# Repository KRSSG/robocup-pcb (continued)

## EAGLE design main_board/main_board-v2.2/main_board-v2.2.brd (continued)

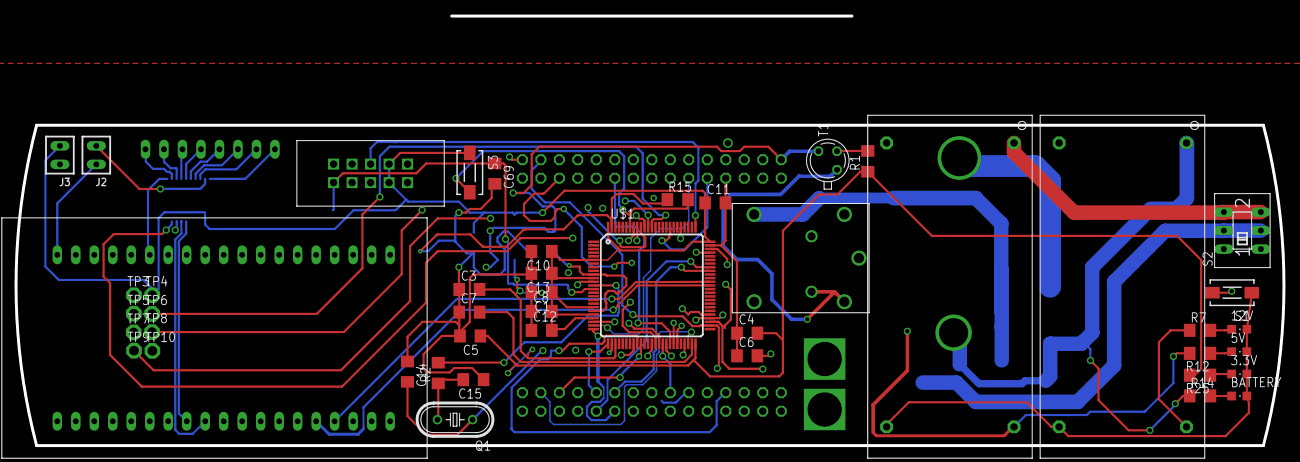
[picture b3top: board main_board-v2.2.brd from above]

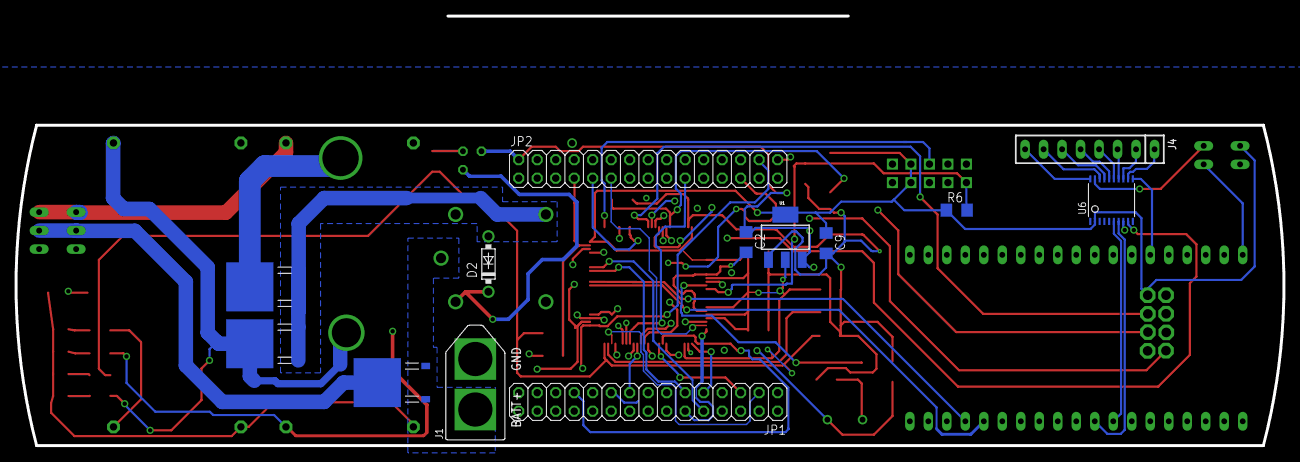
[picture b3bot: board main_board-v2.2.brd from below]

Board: 4 copper layers, 174.2 x 44.0 mm, 59 parts (13 on the bottom side), 70 nets.

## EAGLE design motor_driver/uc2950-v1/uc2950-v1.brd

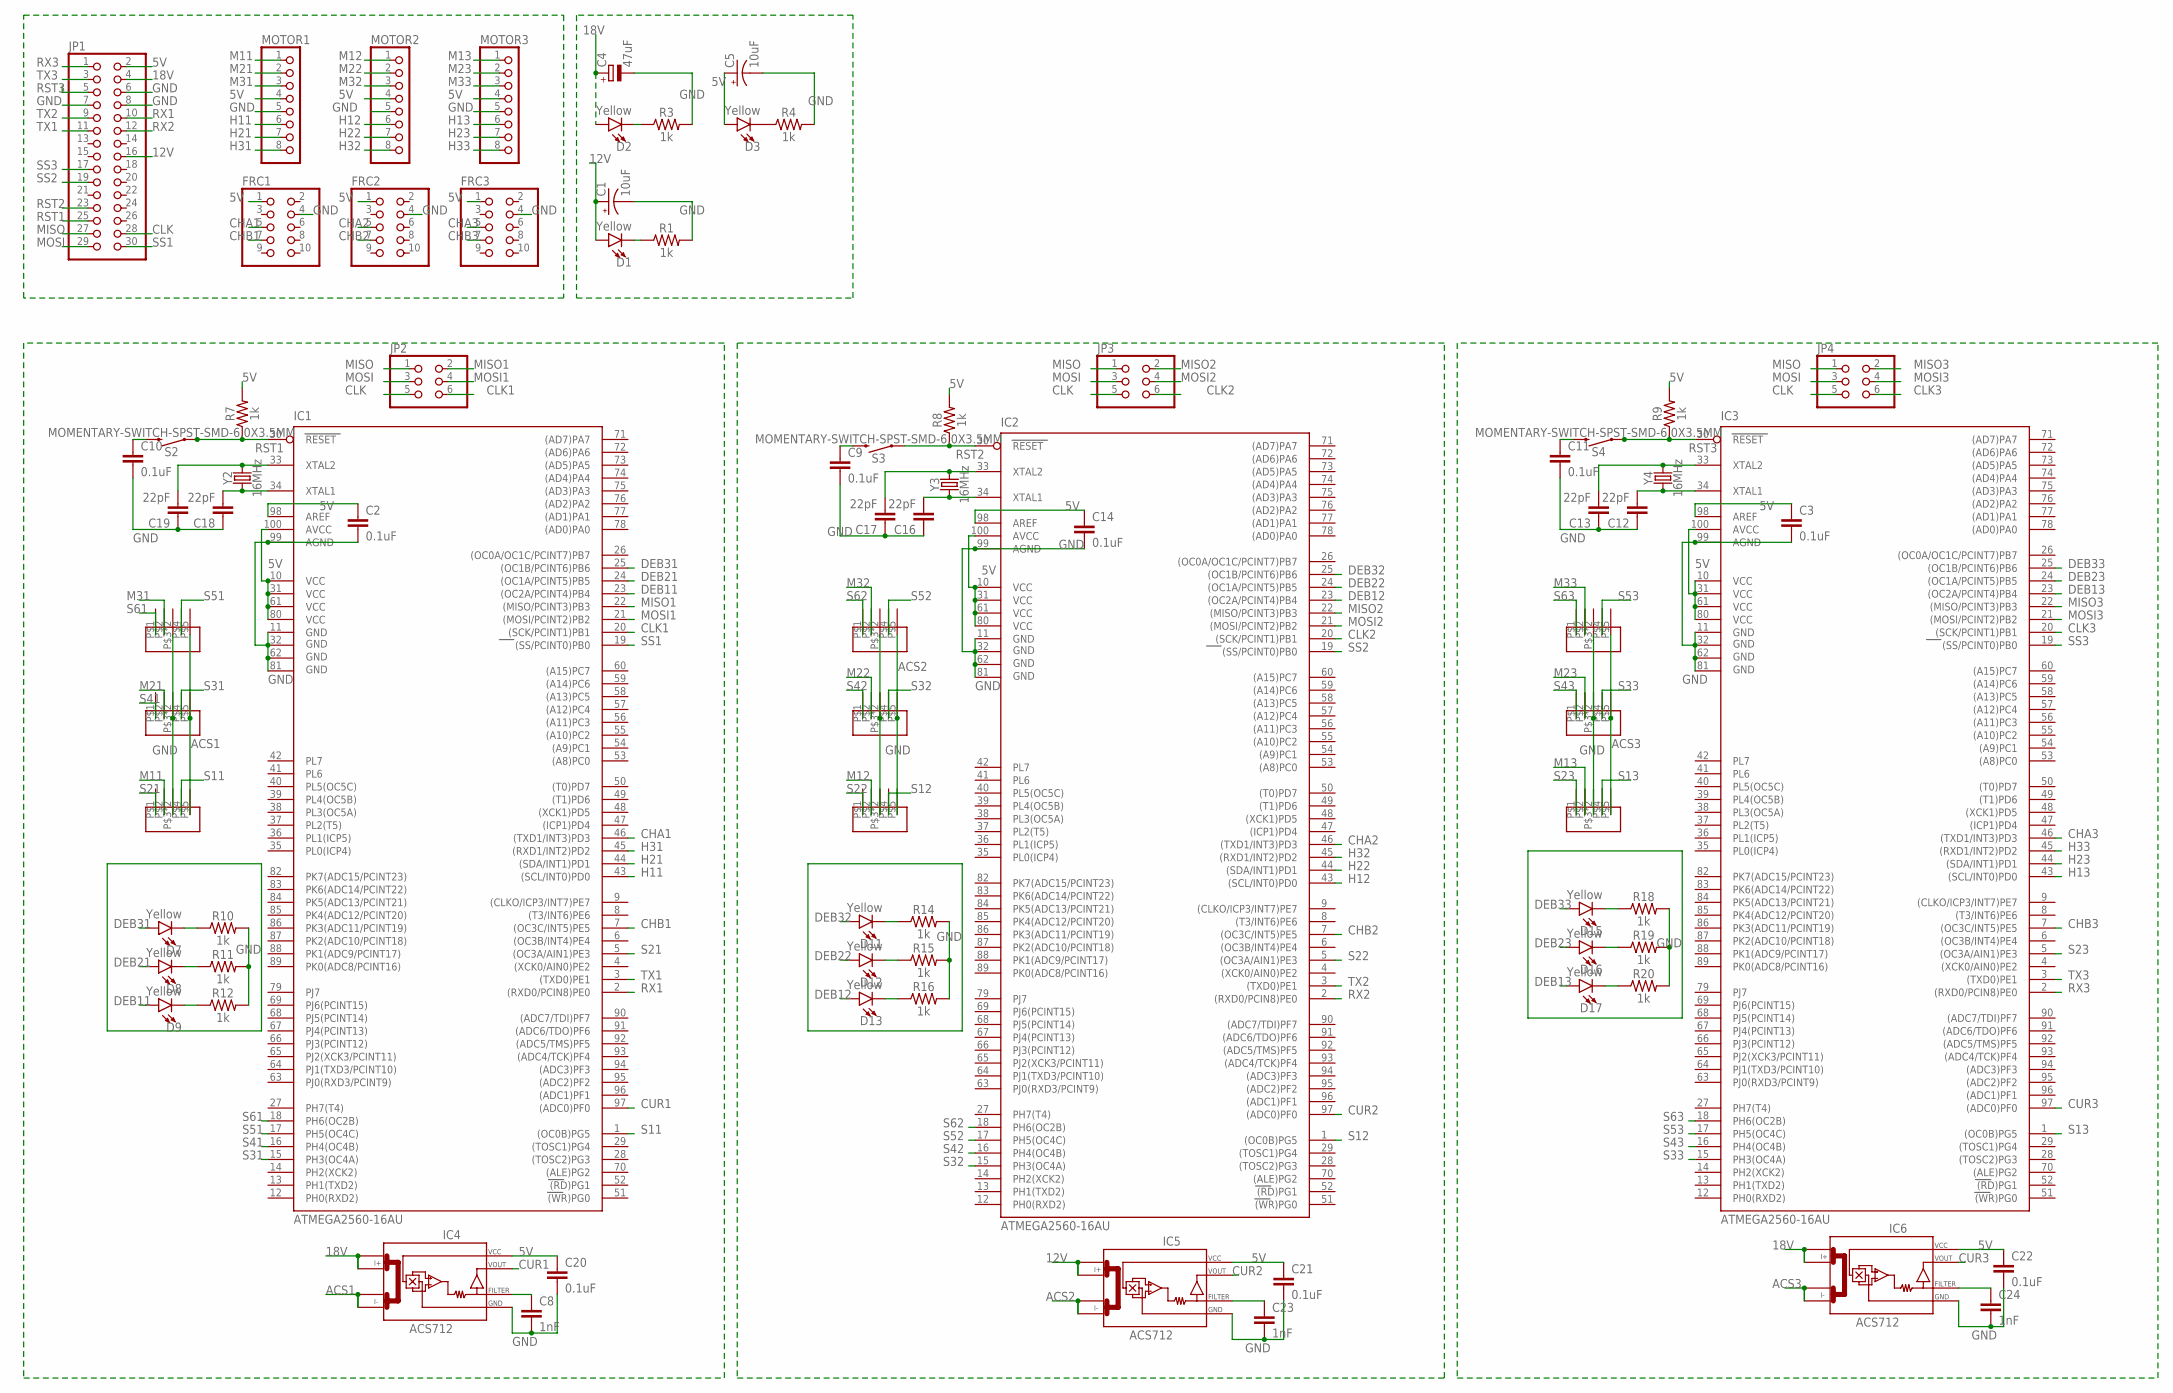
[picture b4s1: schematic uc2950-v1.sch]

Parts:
C1, C5: 10uF; 0603-POLAR
C2, C3, C9, C10, C11, C14, C20, C21, C22: 0.1uF; 0603
C4: 47uF; TAP5-60
C8, C23, C24: 1nF; 0603
C12, C13, C16, C17, C18, C19: 22pF; 0603
D1, D2, D3, D7, D8, D9, D11, D12, D13, D15, D16, D17: Yellow; LED-0603
FRC1, FRC2, FRC3: PINHD-2X5; 2X05
IC1, IC2, IC3: ATMEGA2560-16AU; TQFP100
IC4, IC5, IC6: ACS712; SO08
JP1: PINHD-2X15/90; 2X15/90
JP2, JP3, JP4: PINHD-2X3; 2X03
MIC1, MIC2, MIC3, MIC4, MIC5, MIC6, MIC7, MIC8, MIC9: UC2950
MOTOR1, MOTOR2, MOTOR3: PINHD-1X8; 1X08
R1, R3, R4, R7, R8, R9, R10, R11, R12, R14, R15, R16, R18, R19, R20: 1k; 0603
S2, S3, S4: MOMENTARY-SWITCH-SPST-SMD-6.0X3.5MM; TACTILE_SWITCH_SMD_6.0X3.5MM
Y2, Y3, Y4: 16MHz; CRYSTAL-SMD-5X3.2-4PAD

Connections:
5V: C2.1, C3.1, C5.+, C14.1, C20.1, C21.1, C22.1, D3.A, FRC1.1, FRC2.1, FRC3.1, IC1.10 (VCC), IC1.31 (VCC1), IC1.61 (VCC2), IC1.80 (VCC3), IC1.98 (AREF), IC1.100 (AVCC), IC2.10 (VCC), IC2.31 (VCC1), IC2.61 (VCC2), IC2.80 (VCC3), IC2.98 (AREF), IC2.100 (AVCC), IC3.10 (VCC), IC3.31 (VCC1), IC3.61 (VCC2), IC3.80 (VCC3), IC3.98 (AREF), IC3.100 (AVCC), IC4.8 (VCC), IC5.8 (VCC), IC6.8 (VCC), JP1.2, MOTOR1.4, MOTOR2.4, MOTOR3.4, R7.2, R8.2, R9.2
12V: C1.+, D1.A, IC5.1 (I+_0), IC5.2 (I+_1), JP1.16
18V: C4.+, D2.A, IC4.1 (I+_0), IC4.2 (I+_1), IC6.1 (I+_0), IC6.2 (I+_1), JP1.4
ACS1: IC4.3 (I-_0), IC4.4 (I-_1), MIC1.P$5, MIC2.P$5, MIC3.P$5
ACS2: IC5.3 (I-_0), IC5.4 (I-_1), MIC4.P$5, MIC5.P$5, MIC6.P$5
ACS3: IC6.3 (I-_0), IC6.4 (I-_1), MIC7.P$5, MIC8.P$5, MIC9.P$5
CHA1: FRC1.5, IC1.46 ((TXD1/INT3)PD3)
CHA2: FRC2.5, IC2.46 ((TXD1/INT3)PD3)
CHA3: FRC3.5, IC3.46 ((TXD1/INT3)PD3)
CHB1: FRC1.7, IC1.7 ((OC3C/INT5)PE5)
CHB2: FRC2.7, IC2.7 ((OC3C/INT5)PE5)
CHB3: FRC3.7, IC3.7 ((OC3C/INT5)PE5)
CLK: JP1.28, JP2.5, JP3.5, JP4.5
CLK1: IC1.20 ((SCK/PCINT1)PB1), JP2.6
CLK2: IC2.20 ((SCK/PCINT1)PB1), JP3.6
CLK3: IC3.20 ((SCK/PCINT1)PB1), JP4.6
CUR1: IC1.97 ((ADC0)PF0), IC4.7 (VOUT)
CUR2: IC2.97 ((ADC0)PF0), IC5.7 (VOUT)
CUR3: IC3.97 ((ADC0)PF0), IC6.7 (VOUT)
DEB11: D9.A, IC1.23 ((OC2A/PCINT4)PB4)
DEB12: D13.A, IC2.23 ((OC2A/PCINT4)PB4)
DEB13: D17.A, IC3.23 ((OC2A/PCINT4)PB4)
DEB21: D8.A, IC1.24 ((OC1A/PCINT5)PB5)
DEB22: D12.A, IC2.24 ((OC1A/PCINT5)PB5)
DEB23: D16.A, IC3.24 ((OC1A/PCINT5)PB5)
DEB31: D7.A, IC1.25 ((OC1B/PCINT6)PB6)
DEB32: D11.A, IC2.25 ((OC1B/PCINT6)PB6)
DEB33: D15.A, IC3.25 ((OC1B/PCINT6)PB6)
GND: C1.-, C2.2, C3.2, C4.-, C5.-, C8.2, C9.2, C10.2, C11.2, C12.1, C13.1, C14.2, C16.1, C17.1, C18.1, C19.1, C20.2, C21.2, C22.2, C23.2, C24.2, FRC1.4, FRC2.4, FRC3.4, IC1.11 (GND), IC1.32 (GND1), IC1.62 (GND2), IC1.81 (GND3), IC1.99 (AGND), IC2.11 (GND), IC2.32 (GND1), IC2.62 (GND2), IC2.81 (GND3), IC2.99 (AGND), IC3.11 (GND), IC3.32 (GND1), IC3.62 (GND2), IC3.81 (GND3), IC3.99 (AGND), IC4.5 (GND), IC5.5 (GND), IC6.5 (GND), JP1.6, JP1.7, JP1.8, MIC1.P$3, MIC1.P$6, MIC2.P$3, MIC2.P$6, MIC3.P$3, MIC3.P$6, MIC4.P$3, MIC4.P$6, MIC5.P$3, MIC5.P$6, MIC6.P$3, MIC6.P$6, MIC7.P$3, MIC7.P$6, MIC8.P$3, MIC8.P$6, MIC9.P$3, MIC9.P$6, MOTOR1.5, MOTOR2.5, MOTOR3.5, R1.2, R3.2, R4.2, R10.2, R11.2, R12.2, R14.2, R15.2, R16.2, R18.2, R19.2, R20.2
H11: IC1.43 ((SCL/INT0)PD0), MOTOR1.6
H12: IC2.43 ((SCL/INT0)PD0), MOTOR2.6
H13: IC3.43 ((SCL/INT0)PD0), MOTOR3.6
H21: IC1.44 ((SDA/INT1)PD1), MOTOR1.7
H22: IC2.44 ((SDA/INT1)PD1), MOTOR2.7
H23: IC3.44 ((SDA/INT1)PD1), MOTOR3.7
H31: IC1.45 ((RXD1/INT2)PD2), MOTOR1.8
H32: IC2.45 ((RXD1/INT2)PD2), MOTOR2.8
H33: IC3.45 ((RXD1/INT2)PD2), MOTOR3.8
M11: MIC3.P$2, MOTOR1.1
M12: MIC6.P$2, MOTOR2.1
M13: MIC7.P$2, MOTOR3.1
M21: MIC2.P$2, MOTOR1.2
M22: MIC5.P$2, MOTOR2.2
M23: MIC8.P$2, MOTOR3.2
M31: MIC1.P$2, MOTOR1.3
M32: MIC4.P$2, MOTOR2.3
M33: MIC9.P$2, MOTOR3.3
MISO: JP1.27, JP2.1, JP3.1, JP4.1
MISO1: IC1.22 ((MISO/PCINT3)PB3), JP2.2
MISO2: IC2.22 ((MISO/PCINT3)PB3), JP3.2
MISO3: IC3.22 ((MISO/PCINT3)PB3), JP4.2
MOSI: JP1.29, JP2.3, JP3.3, JP4.3
MOSI1: IC1.21 ((MOSI/PCINT2)PB2), JP2.4
MOSI2: IC2.21 ((MOSI/PCINT2)PB2), JP3.4
MOSI3: IC3.21 ((MOSI/PCINT2)PB2), JP4.4
unnamed: D1.C, R1.1
unnamed: D2.C, R3.1
unnamed: D3.C, R4.1
unnamed: C10.1, S2.2
unnamed: C11.1, S4.2
unnamed: C9.1, S3.2
unnamed: C19.2, IC1.33 (XTAL2), Y2.3 (2)
unnamed: C17.2, IC2.33 (XTAL2), Y3.3 (2)
unnamed: C16.2, IC2.34 (XTAL1), Y3.1
unnamed: C18.2, IC1.34 (XTAL1), Y2.1
unnamed: C13.2, IC3.33 (XTAL2), Y4.3 (2)
unnamed: C12.2, IC3.34 (XTAL1), Y4.1
unnamed: C8.1, IC4.6 (FILTER)
unnamed: C23.1, IC5.6 (FILTER)
unnamed: C24.1, IC6.6 (FILTER)
unnamed: D7.C, R10.1
unnamed: D8.C, R11.1
unnamed: D9.C, R12.1
unnamed: D11.C, R14.1
unnamed: D12.C, R15.1
unnamed: D13.C, R16.1
unnamed: D15.C, R18.1
unnamed: D16.C, R19.1
unnamed: D17.C, R20.1
RST1: IC1.30 (RESET), JP1.25, R7.1, S2.1
RST2: IC2.30 (RESET), JP1.23, R8.1, S3.1
RST3: IC3.30 (RESET), JP1.5, R9.1, S4.1
RX1: IC1.2 ((RXD0/PCIN8)PE0), JP1.10
RX2: IC2.2 ((RXD0/PCIN8)PE0), JP1.12
RX3: IC3.2 ((RXD0/PCIN8)PE0), JP1.1
S11: IC1.1 ((OC0B)PG5), MIC3.P$4
S12: IC2.1 ((OC0B)PG5), MIC6.P$4
S13: IC3.1 ((OC0B)PG5), MIC7.P$4
S21: IC1.5 ((OC3A/AIN1)PE3), MIC3.P$1
S22: IC2.5 ((OC3A/AIN1)PE3), MIC6.P$1
S23: IC3.5 ((OC3A/AIN1)PE3), MIC7.P$1
S31: IC1.15 (PH3(OC4A)), MIC2.P$4
S32: IC2.15 (PH3(OC4A)), MIC5.P$4
S33: IC3.15 (PH3(OC4A)), MIC8.P$4
S41: IC1.16 (PH4(OC4B)), MIC2.P$1
S42: IC2.16 (PH4(OC4B)), MIC5.P$1
S43: IC3.16 (PH4(OC4B)), MIC8.P$1
S51: IC1.17 (PH5(OC4C)), MIC1.P$4
S52: IC2.17 (PH5(OC4C)), MIC4.P$4
S53: IC3.17 (PH5(OC4C)), MIC9.P$4
S61: IC1.18 (PH6(OC2B)), MIC1.P$1
S62: IC2.18 (PH6(OC2B)), MIC4.P$1
S63: IC3.18 (PH6(OC2B)), MIC9.P$1
SS1: IC1.19 ((SS/PCINT0)PB0), JP1.30
SS2: IC2.19 ((SS/PCINT0)PB0), JP1.19
SS3: IC3.19 ((SS/PCINT0)PB0), JP1.17
TX1: IC1.3 ((TXD0)PE1), JP1.11
TX2: IC2.3 ((TXD0)PE1), JP1.9
TX3: IC3.3 ((TXD0)PE1), JP1.3

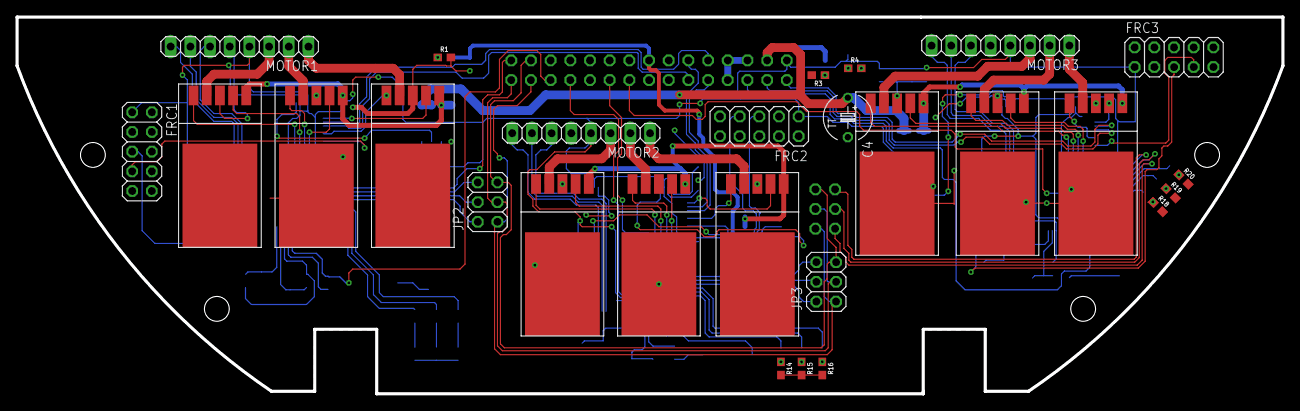
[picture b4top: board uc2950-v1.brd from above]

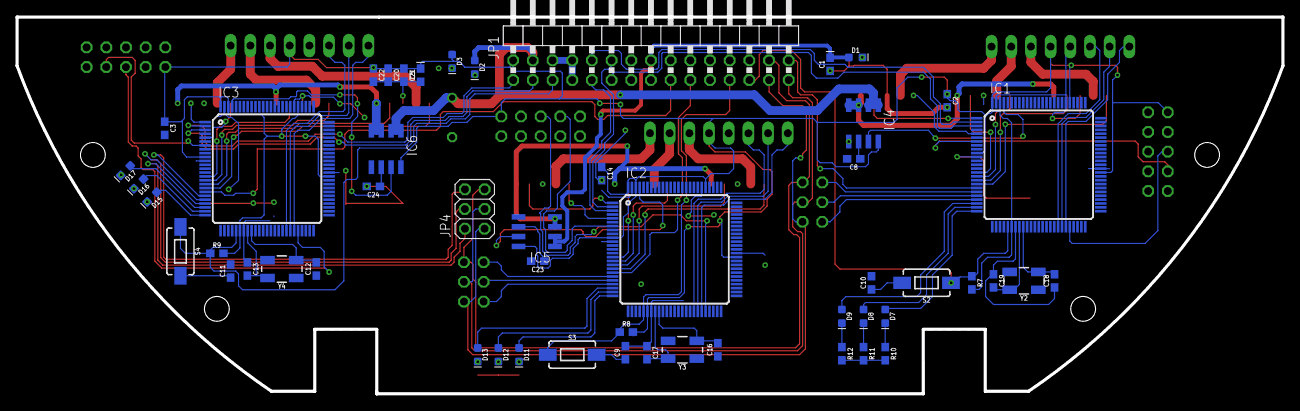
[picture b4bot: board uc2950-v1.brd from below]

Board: 2 copper layers, 163.3 x 48.6 mm, 79 parts (52 on the bottom side), 109 nets.

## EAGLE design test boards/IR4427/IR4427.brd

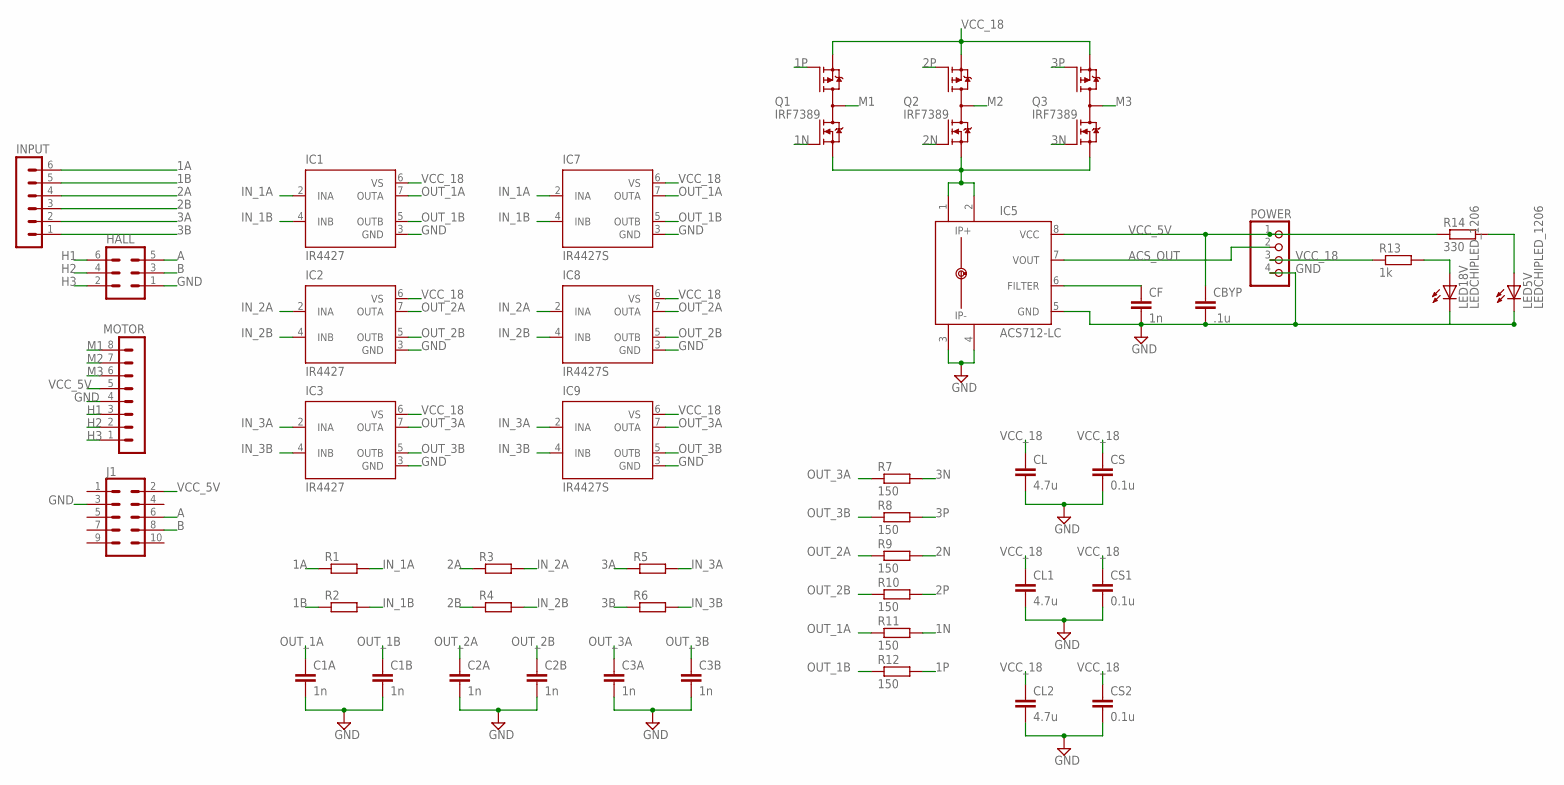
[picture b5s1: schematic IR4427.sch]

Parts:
C1A, C1B, C2A, C2B, C3A, C3B: 1n; C1206
CBYP: .1u; C1206
CF: 1n; C1206
CL, CL1, CL2: 4.7u; C1206
CS, CS1, CS2: 0.1u; C1206
HALL: MA03-2
IC1, IC2, IC3: IR4427; DIL08
IC5: ACS712-LC; SOIC8
IC7, IC8, IC9: IR4427S; SO08
INPUT: MA06-1
J1: CONN_05X2SHD_LOCK; 2X5-SHROUDED_LOCK
LED5V, LED18V: LEDCHIPLED_1206; CHIPLED_1206
MOTOR: MA08-1
POWER: PINHD-1X4; 1X04
Q1, Q2, Q3: IRF7389; SO08-IRF
R1, R2, R3, R4, R5, R6: RR1206; R1206
R7, R8, R9, R10, R11, R12: 150; R1206
R13: 1k; R1206
R14: 330; R1206

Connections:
1A: INPUT.6, R1.1
1B: INPUT.5, R2.1
1N: Q1.2 (N-G), R11.2
1P: Q1.4 (P-G), R12.2
2A: INPUT.4, R3.1
2B: INPUT.3, R4.1
2N: Q2.2 (N-G), R9.2
2P: Q2.4 (P-G), R10.2
3A: INPUT.2, R5.1
3B: INPUT.1, R6.1
3N: Q3.2 (N-G), R7.2
3P: Q3.4 (P-G), R8.2
A: HALL.5, J1.6
ACS_OUT: IC5.7 (VOUT), POWER.2
B: HALL.3, J1.8
GND: C1A.2, C1B.2, C2A.2, C2B.2, C3A.2, C3B.2, CBYP.2, CF.2, CL.2, CL1.2, CL2.2, CS.2, CS1.2, CS2.2, HALL.1, IC1.3 (GND), IC2.3 (GND), IC3.3 (GND), IC5.3 (IP-), IC5.4 (IP-1), IC5.5 (GND), IC7.3 (GND), IC8.3 (GND), IC9.3 (GND), J1.3, LED5V.C, LED18V.C, MOTOR.4, POWER.4
H1: HALL.6, MOTOR.3
H2: HALL.4, MOTOR.2
H3: HALL.2, MOTOR.1
IN_1A: IC1.2 (INA), IC7.2 (INA), R1.2
IN_1B: IC1.4 (INB), IC7.4 (INB), R2.2
IN_2A: IC2.2 (INA), IC8.2 (INA), R3.2
IN_2B: IC2.4 (INB), IC8.4 (INB), R4.2
IN_3A: IC3.2 (INA), IC9.2 (INA), R5.2
IN_3B: IC3.4 (INB), IC9.4 (INB), R6.2
M1: MOTOR.8, Q1.5 (D), Q1.6 (D), Q1.7 (D), Q1.8 (D)
M2: MOTOR.7, Q2.5 (D), Q2.6 (D), Q2.7 (D), Q2.8 (D)
M3: MOTOR.6, Q3.5 (D), Q3.6 (D), Q3.7 (D), Q3.8 (D)
unnamed: IC5.1 (IP+), IC5.2 (IP+1), Q1.1 (N-S), Q2.1 (N-S), Q3.1 (N-S)
unnamed: LED18V.A, R13.2
unnamed: CF.1, IC5.6 (FILTER)
unnamed: LED5V.A, R14.2
OUT_1A: C1A.1, IC1.7 (OUTA), IC7.7 (OUTA), R11.1
OUT_1B: C1B.1, IC1.5 (OUTB), IC7.5 (OUTB), R12.1
OUT_2A: C2A.1, IC2.7 (OUTA), IC8.7 (OUTA), R9.1
OUT_2B: C2B.1, IC2.5 (OUTB), IC8.5 (OUTB), R10.1
OUT_3A: C3A.1, IC3.7 (OUTA), IC9.7 (OUTA), R7.1
OUT_3B: C3B.1, IC3.5 (OUTB), IC9.5 (OUTB), R8.1
VCC_5V: CBYP.1, IC5.8 (VCC), J1.2, MOTOR.5, POWER.1, R14.1
VCC_18: CL.1, CL1.1, CL2.1, CS.1, CS1.1, CS2.1, IC1.6 (VS), IC2.6 (VS), IC3.6 (VS), IC7.6 (VS), IC8.6 (VS), IC9.6 (VS), POWER.3, Q1.3 (P-S), Q2.3 (P-S), Q3.3 (P-S), R13.1

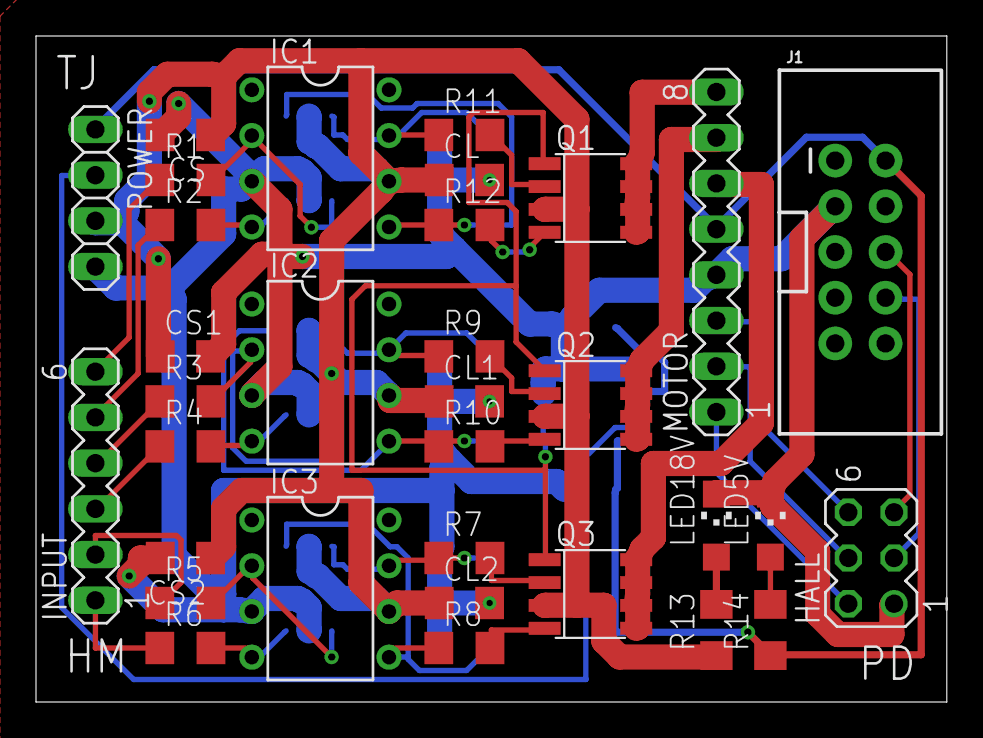
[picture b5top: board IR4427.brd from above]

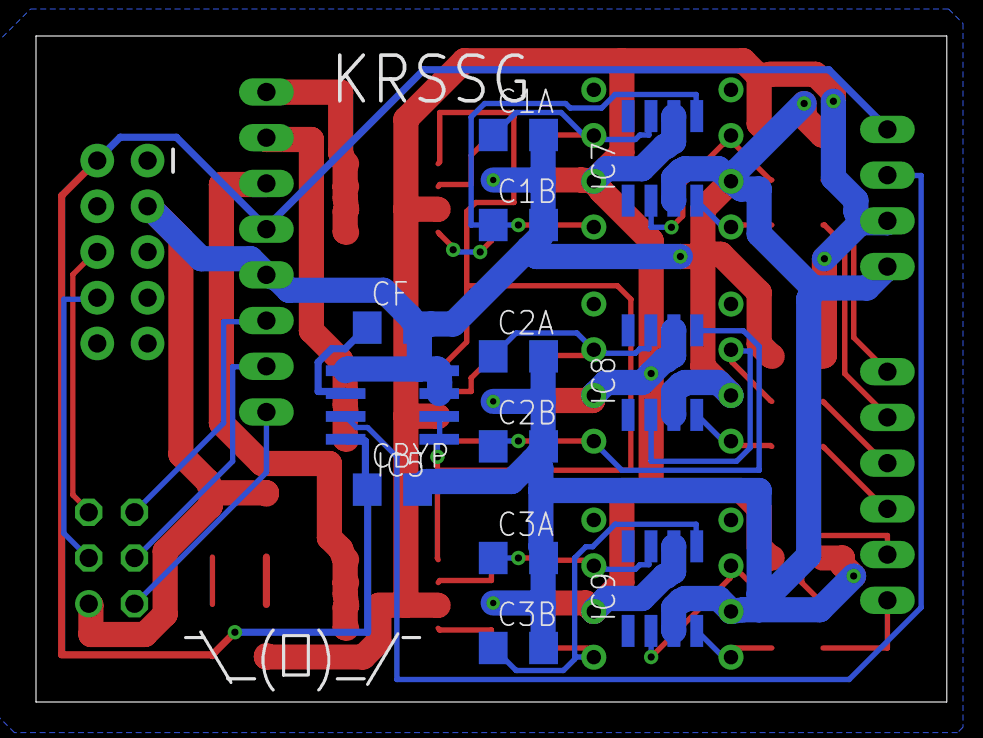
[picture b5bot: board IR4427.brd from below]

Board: 2 copper layers, 50.6 x 37.0 mm, 45 parts (12 on the bottom side), 40 nets.

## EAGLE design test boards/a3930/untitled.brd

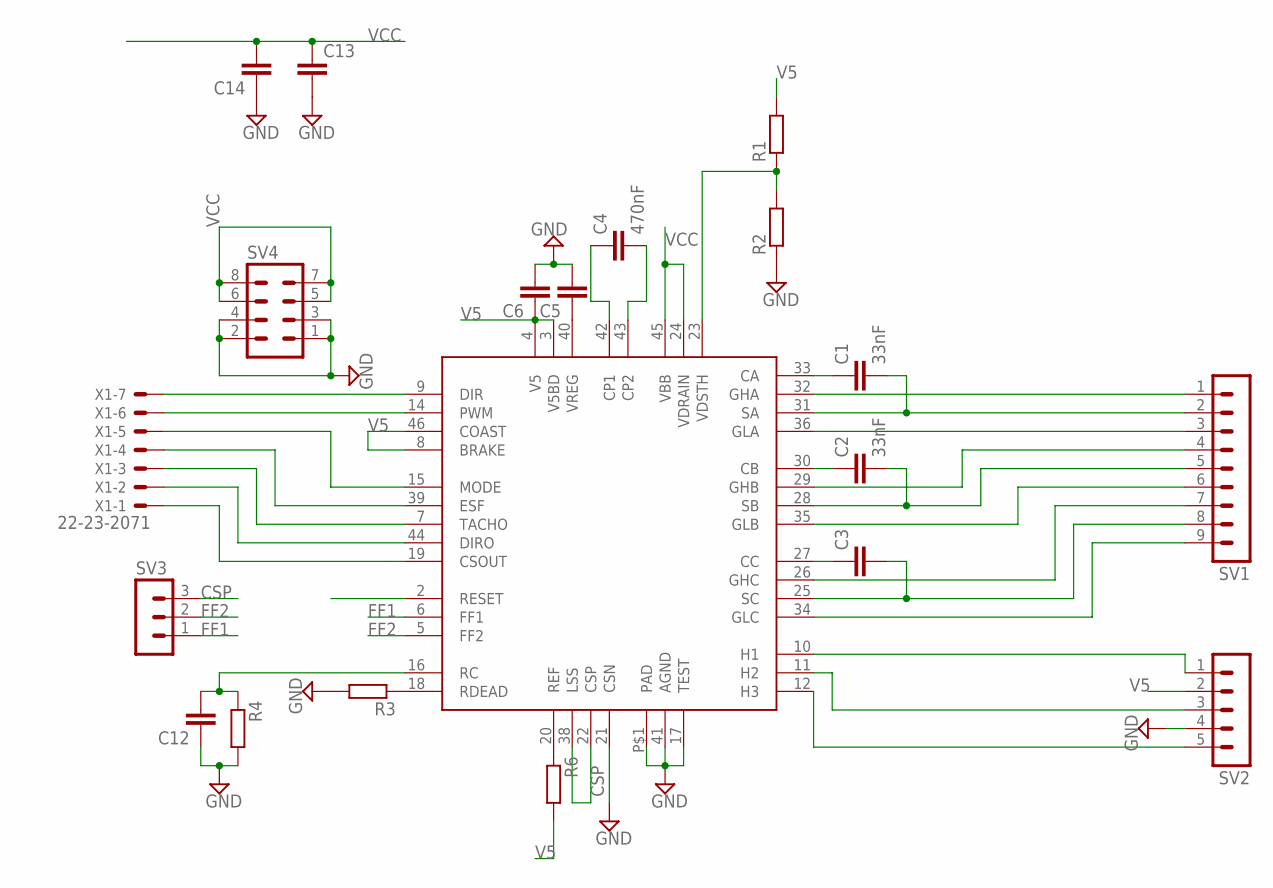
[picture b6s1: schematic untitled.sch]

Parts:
C1, C2: 33nF; C0603
C3: C-EUC0603; C0603
C4: 470nF; C0805
C5, C6, C12, C14: C-EUC1206; C1206
C13: C-EU025-050X050; C025-050X050
R1, R2, R3, R4, R6: R-EU_R1206; R1206
SV1: MA09-1
SV2: MA05-1
SV3: MA03-1
SV4: MA04-2
U$1: A3930; TQFP48
X1: 22-23-2071

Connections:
CSP: SV3.3, U$1.22 (CSP), U$1.38 (LSS)
FF1: SV3.1, U$1.6 (FF1)
FF2: SV3.2, U$1.5 (FF2)
GND: C5.2, C6.2, C12.1, C13.2, C14.1, R2.1, R3.2, R4.2, SV2.4, SV4.1, SV4.2, SV4.3, SV4.4, U$1.17 (TEST), U$1.21 (CSN), U$1.41 (AGND), U$1.P$1 (PAD)
unnamed: SV1.1, U$1.32 (GHA)
unnamed: C1.2, SV1.2, U$1.31 (SA)
unnamed: SV1.3, U$1.36 (GLA)
unnamed: SV1.4, U$1.29 (GHB)
unnamed: C2.2, SV1.5, U$1.28 (SB)
unnamed: SV1.6, U$1.35 (GLB)
unnamed: SV1.7, U$1.26 (GHC)
unnamed: C3.2, SV1.8, U$1.25 (SC)
unnamed: SV1.9, U$1.34 (GLC)
unnamed: C1.1, U$1.33 (CA)
unnamed: C2.1, U$1.30 (CB)
unnamed: C3.1, U$1.27 (CC)
unnamed: C4.1, U$1.42 (CP1)
unnamed: C4.2, U$1.43 (CP2)
unnamed: SV2.1, U$1.10 (H1)
unnamed: SV2.3, U$1.11 (H2)
unnamed: SV2.5, U$1.12 (H3)
unnamed: R1.1, R2.2, U$1.23 (VDSTH)
unnamed: C5.1, U$1.40 (VREG)
unnamed: U$1.9 (DIR), X1.7
unnamed: R3.1, U$1.18 (RDEAD)
unnamed: C12.2, R4.1, U$1.16 (RC)
unnamed: U$1.14 (PWM), X1.6
unnamed: R6.1, U$1.20 (REF)
unnamed: U$1.15 (MODE), X1.5
unnamed: U$1.39 (ESF), X1.4
unnamed: U$1.7 (TACHO), X1.3
unnamed: U$1.44 (DIRO), X1.2
unnamed: U$1.19 (CSOUT), X1.1
V5: C6.1, R1.2, R6.2, SV2.2, U$1.3 (V5BD), U$1.4 (V5), U$1.8 (BRAKE), U$1.46 (COAST)
VCC: C13.1, C14.2, SV4.5, SV4.6, SV4.7, SV4.8, U$1.24 (VDRAIN), U$1.45 (VBB)

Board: 2 copper layers, 20 parts (6 on the bottom side), 35 nets, no tracks yet.

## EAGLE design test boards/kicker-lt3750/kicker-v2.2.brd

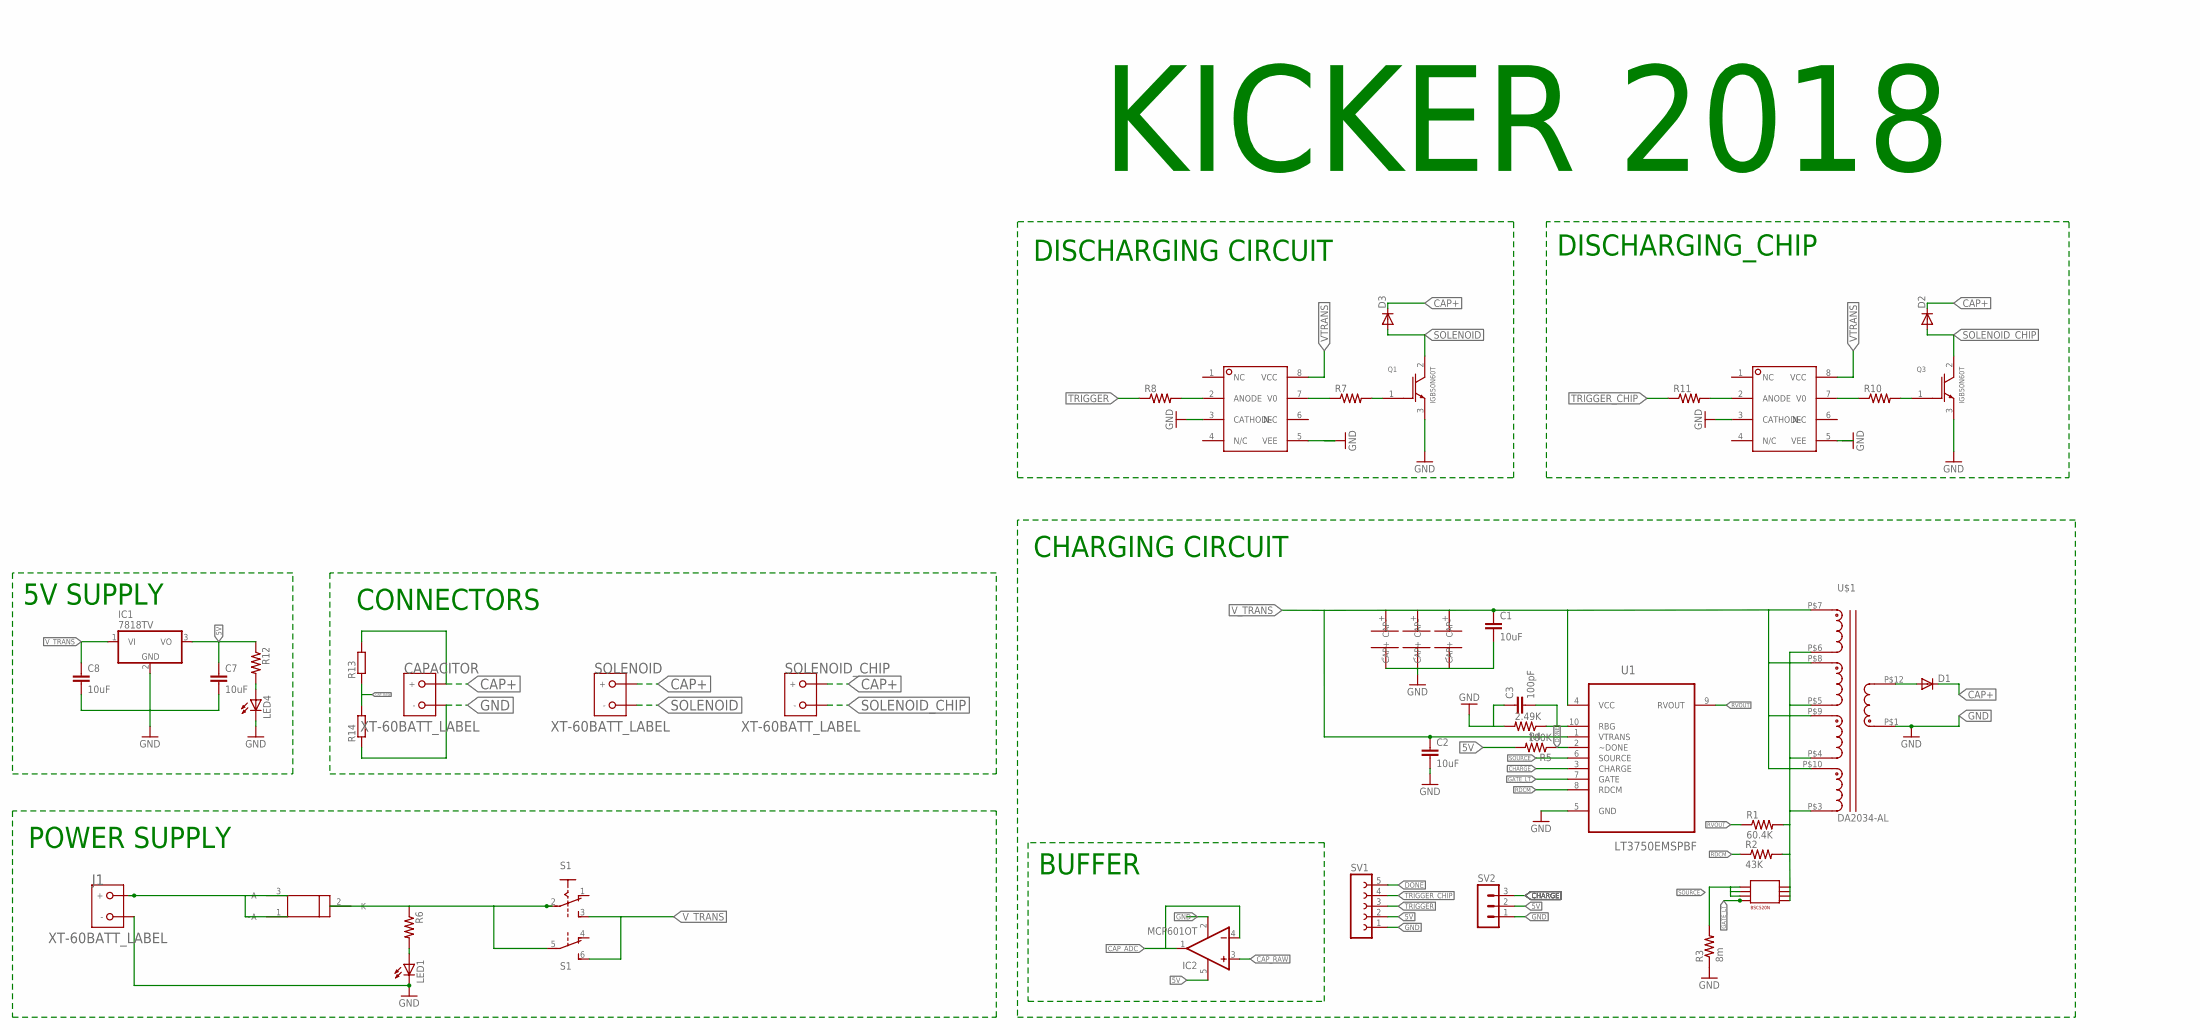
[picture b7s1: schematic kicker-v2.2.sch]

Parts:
C1, C2, C7, C8: 10uF; C1206
C3: 100pF; C1206
CAPACITOR: XT-60BATT_LABEL; XT-60
D1, D2, D3: DIODE-DO214AA; DO214AA
IC1: 7818TV; TO220V
IC2: MCP601OT; SOT23-5
J1: XT-60BATT_LABEL; XT-60
LED1, LED4: LEDCHIPLED_1206; CHIPLED_1206
Q1, Q3: IGB50N60T; TO254P1524X457-3N-2-V
R1: 60.4K; M1206
R2: 43K; M1206
R3: 8m; M1206
R4: 2.49K; M1206
R5: 100K; M1206
R6, R7, R8, R10, R11, R12: R-US_M1206; M1206
R13, R14: R-EU_R0805; R0805
S1: A68-A31
SOLENOID: XT-60BATT_LABEL; XT-60
SOLENOID_CHIP: XT-60BATT_LABEL; XT-60
SV1: FE05-1
SV2: MA03-1
U1: LT3750EMSPBF; SOP50P490X110-10N
U3: LP38690DT-3.3; TO228P1042X238-3N
U$1: DA2034-AL
U$2, U$3, U$4: 56uF; SVP_F12
U$5: BSC520N; PG-TDSON-8
U$6, U$7: HCPL-3120-300E; DIL08

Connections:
5V: C7.1, IC1.3 (VO), IC2.5 (V+), R5.2, R12.1, SV1.2, SV2.2
CAP+: CAPACITOR.BATT (+), D1.C, D2.C, D3.C, R13.2, SOLENOID.BATT (+), SOLENOID_CHIP.BATT (+)
CAP_ADC: IC2.1 (OUT), IC2.4 (-IN)
CAP_RAW: IC2.3 (+IN), R13.1, R14.2
CHARGE: SV2.3, U1.3 (CHARGE)
DONE: R5.1, SV1.5, U1.2 (~DONE)
GATE_LT: U1.7 (GATE), U$5.G
GND: C1.2, C2.2, C3.1, C7.2, C8.2, CAPACITOR.GND (-), IC1.2 (GND), IC2.2 (V-), J1.GND (-), LED1.C, LED4.C, Q1.3 (EMITTER), Q3.3 (EMITTER), R3.1, R4.2, R14.1, SV1.1, SV2.1, U1.5 (GND), U$1.P$1 (1), U$2.- (CAP-), U$3.- (CAP-), U$4.- (CAP-), U$6.3 (CATHODE), U$6.5 (VEE), U$7.3 (CATHODE), U$7.5 (VEE)
unnamed: D1.A, U$1.P$12 (12)
unnamed: R7.1, U$6.7 (V0)
unnamed: C3.2, R4.1, U1.10 (RBG)
unnamed: R6.1, S1.2, S1.5, U3.2 (K)
unnamed: Q1.1 (GATE), R7.2
unnamed: R8.2, U$6.2 (ANODE)
unnamed: LED1.A, R6.2
unnamed: R10.1, U$7.7 (V0)
unnamed: Q3.1 (GATE), R10.2
unnamed: R11.2, U$7.2 (ANODE)
unnamed: LED4.A, R12.2
RDCM: R2.1, U1.8 (RDCM)
RVOUT: R1.1, U1.9 (RVOUT)
SINK: R1.2, R2.2, U$1.P$3 (3), U$1.P$4 (4), U$1.P$5 (5), U$1.P$6 (6), U$5.D1, U$5.D2, U$5.D3, U$5.D4
SOLENOID: D3.A, Q1.2 (COLLECTOR), SOLENOID.GND (-)
SOLENOID_CHIP: D2.A, Q3.2 (COLLECTOR), SOLENOID_CHIP.GND (-)
SOURCE: R3.2, U1.6 (SOURCE), U$5.S1, U$5.S2, U$5.S3
TRIGGER: R8.1, SV1.3
TRIGGER_CHIP: R11.1, SV1.4
VIN: J1.BATT (+), U3.1 (~A), U3.3 (A)
VTRANS: U$6.8 (VCC), U$7.8 (VCC)
V_TRANS: C1.1, C2.1, C8.1, IC1.1 (VI), S1.3 (S), S1.6 (S), U1.1 (VTRANS), U1.4 (VCC), U$1.P$7 (7), U$1.P$8 (8), U$1.P$9 (9), U$1.P$10 (10), U$2.+ (CAP+), U$3.+ (CAP+), U$4.+ (CAP+)

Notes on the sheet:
DISCHARGING CIRCUIT
POWER SUPPLY
CHARGING CIRCUIT
DISCHARGING_CHIP
5V SUPPLY
CONNECTORS
KICKER 2018
BUFFER

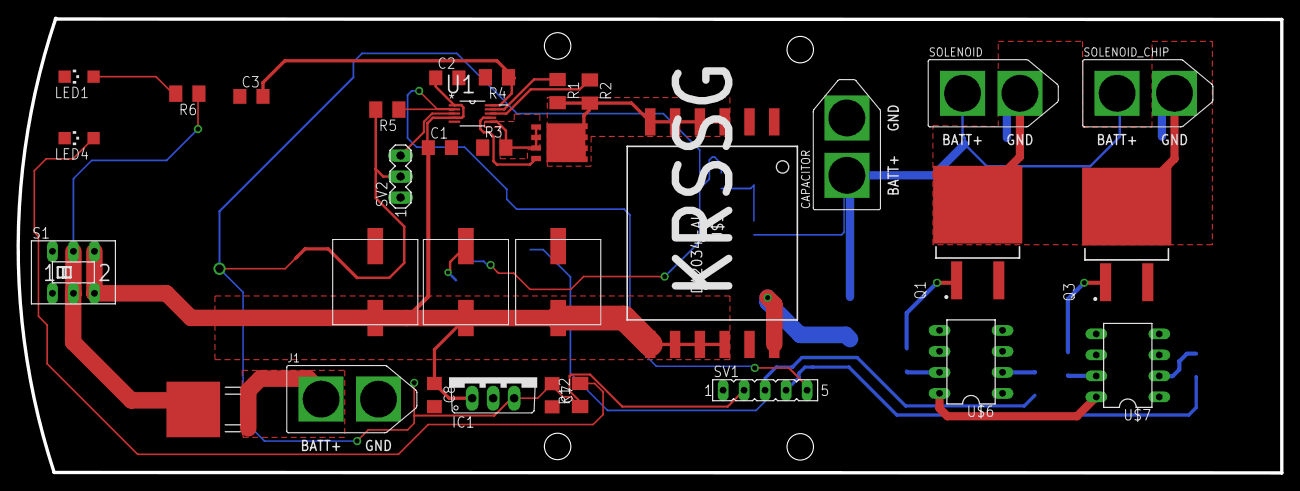
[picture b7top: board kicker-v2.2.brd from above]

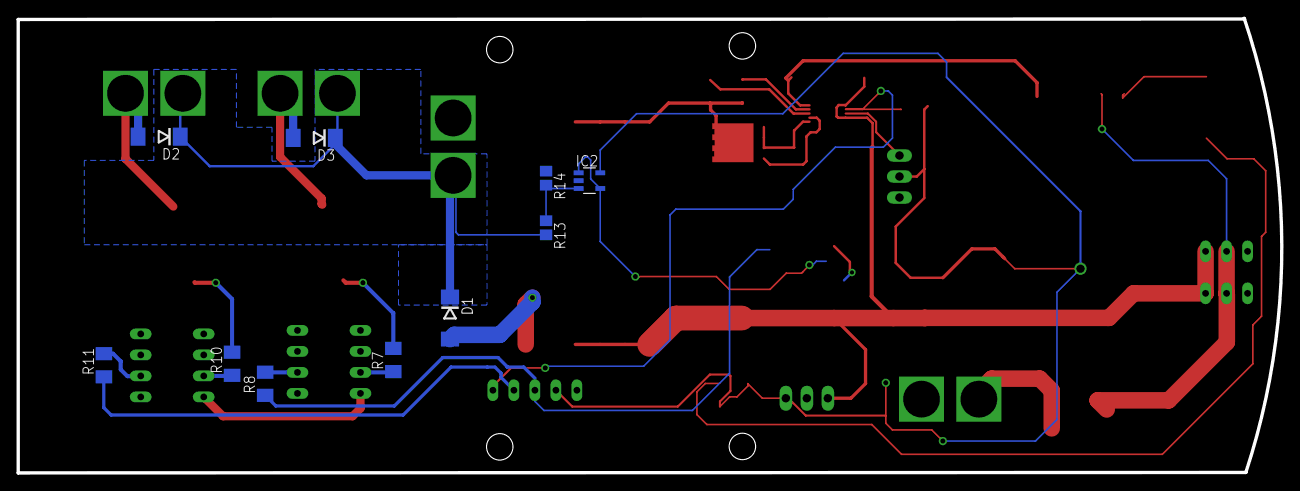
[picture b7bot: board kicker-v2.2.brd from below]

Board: 2 copper layers, 152.8 x 55.0 mm, 43 parts (10 on the bottom side), 30 nets.
